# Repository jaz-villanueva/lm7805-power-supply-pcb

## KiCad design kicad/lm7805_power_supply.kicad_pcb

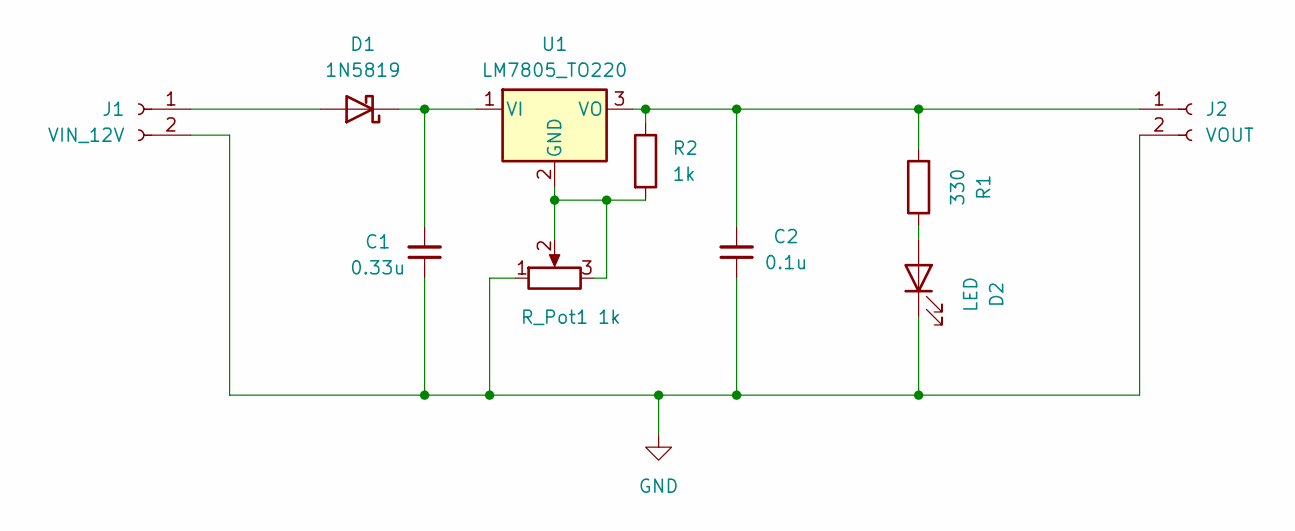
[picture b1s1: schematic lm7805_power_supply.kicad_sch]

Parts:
C1: 0.33u; C_1206_3216Metric
C2: 0.1u; C_0805_2012Metric
D1: 1N5819; D_SMA
D2: LED; LED_1206_3216Metric
J1: VIN_12V; JST_PH_S2B-PH-SM4-TB_1x02-1MP_P2.00mm_Horizontal
J2: VOUT; JST_PH_S2B-PH-SM4-TB_1x02-1MP_P2.00mm_Horizontal
R1: 330; R_0805_2012Metric
R2: 1k; R_0805_2012Metric
R_Pot1: 1k; Potentiometer_Bourns_3314G_Vertical
U1: LM7805_TO220; TO-252-3_TabPin2

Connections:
GND: C1.1, C2.1, D2.1 (K), J1.2, J2.2, R_Pot1.1
unnamed: D1.2 (A), J1.1
unnamed: C1.2, D1.1 (K), U1.1 (VI)
unnamed: D2.2 (A), R1.1
unnamed: C2.2, J2.1, R1.2, R2.1, U1.3 (VO)
unnamed: R2.2, R_Pot1.2, R_Pot1.3, U1.2 (GND)

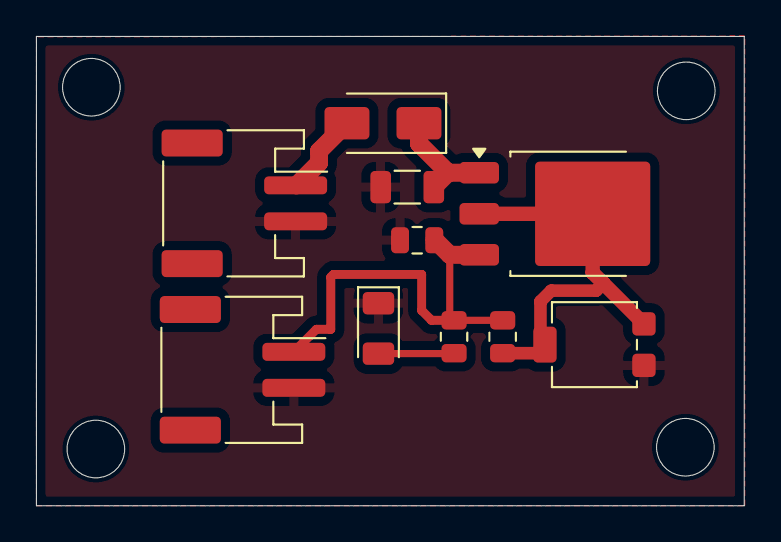
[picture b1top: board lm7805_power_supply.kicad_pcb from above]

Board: 2 copper layers, 39.3 x 26.1 mm, 10 parts (0 on the bottom side), 6 nets.

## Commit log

2026-04-20 Create setup
2026-04-20 fix setup
